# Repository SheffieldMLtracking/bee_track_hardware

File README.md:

# bee_track_hardware
The PCBs and 3d print models etc for the bee tracking system

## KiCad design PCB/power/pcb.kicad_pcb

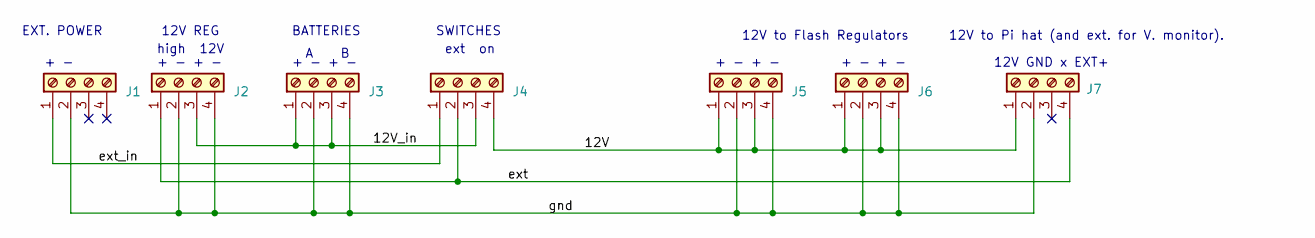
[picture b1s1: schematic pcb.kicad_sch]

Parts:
J1, J2, J3, J4, J5, J6, J7: Screw_Terminal_01x04; TerminalBlock_RND_205-00278_1x04_P5.00mm_Vertical

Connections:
/12V: J4.4, J5.1, J5.3, J6.1, J6.3, J7.1
/12V_in: J2.3, J3.1, J3.3, J4.3
/ext: J2.1, J4.2, J7.4
/ext_in: J1.1, J4.1
/gnd: J1.2, J2.2, J2.4, J3.2, J3.4, J5.2, J5.4, J6.2, J6.4, J7.2

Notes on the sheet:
high 12V
12V to Flash Regulators
12V REG
+ - + -
BATTERIES
12V to Pi hat (and ext. for V. monitor).
A B
12V GND x EXT+
EXT. POWER
ext on
+ -
SWITCHES

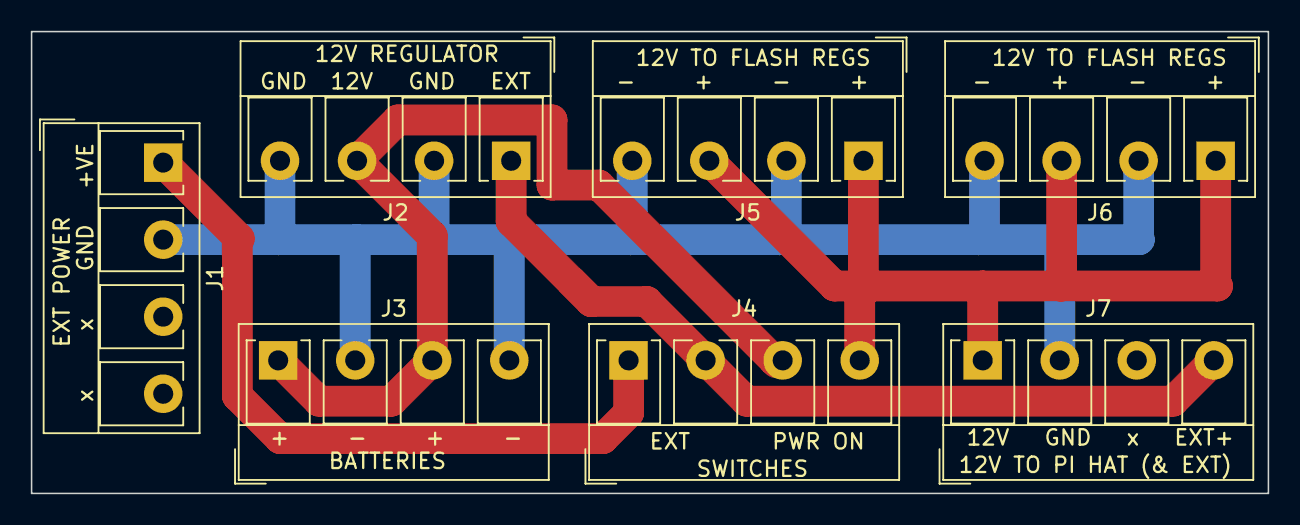
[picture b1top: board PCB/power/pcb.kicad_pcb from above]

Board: 2 copper layers, 80.3 x 30.0 mm, 7 parts (0 on the bottom side), 5 nets.

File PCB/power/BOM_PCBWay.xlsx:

|  |  | xxxx xxxx xxxxx xxPCS BOM (Sample Bill of Materials)
Item # | *Designator | *Qty | Manufacturer | *Mfg Part # | Description / Value | *Package/Footprint | Type | Your Instructions / Notes
1 | J1,J2,J3,J4,J5,J6,J7 | 7 | CAMDENBOSS | CTB5202/4 | Standard Terminal Block, Wire to Board, CTB5202, 4 Contacts, 5 mm, Terminal Blo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 | 5mm pitch, 4 pins | thru-hole | Please place with holes facing OUTWARDS. | https://uk.farnell.com/camdenboss/ctb5202-4/terminal-block-w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

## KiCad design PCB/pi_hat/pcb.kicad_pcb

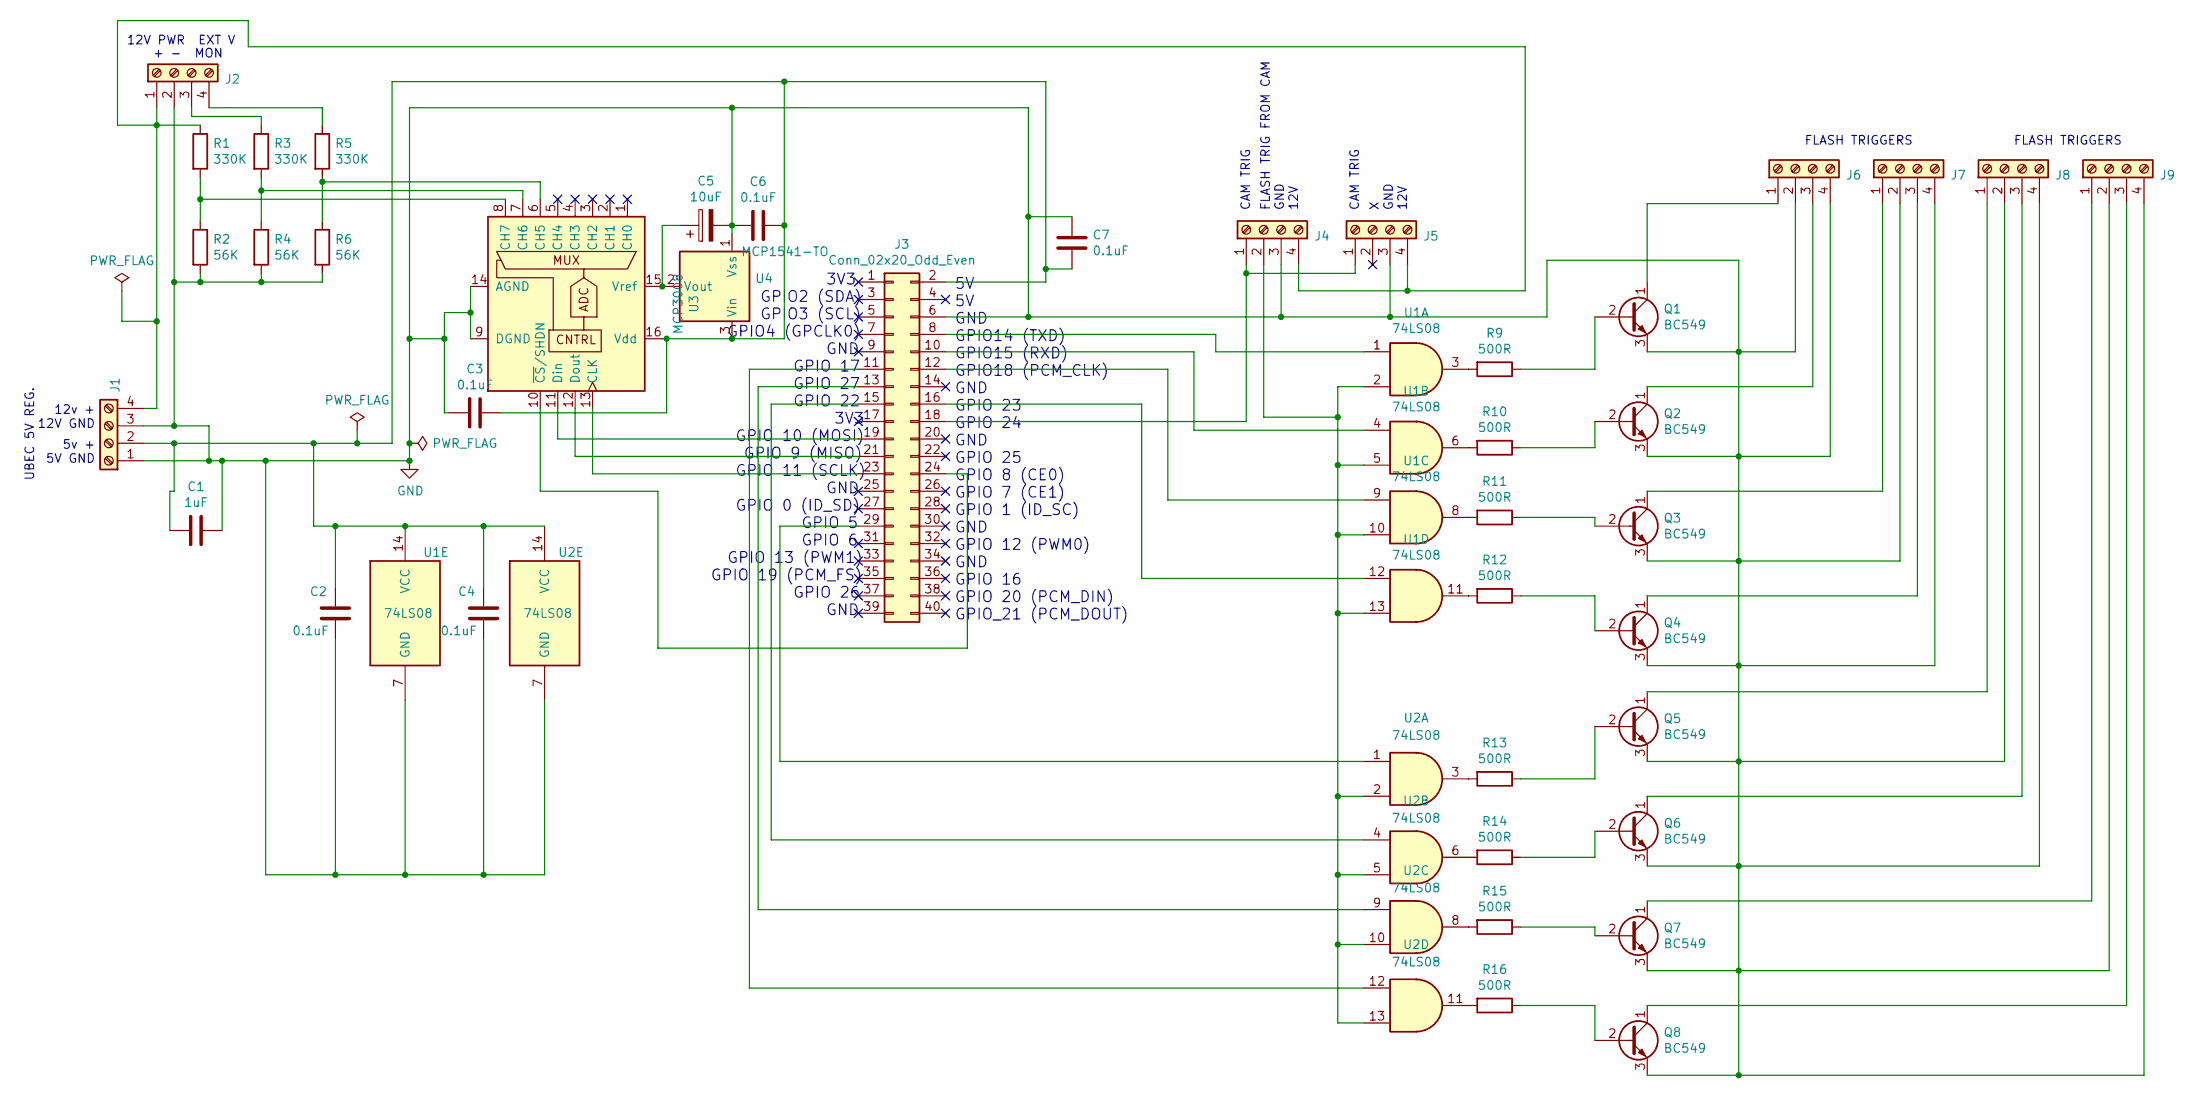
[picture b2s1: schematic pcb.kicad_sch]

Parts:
C1: 1uF; C_0402_1005Metric
C2, C3, C4, C6, C7: 0.1uF; C_0402_1005Metric
C5: 10uF; CP_Elec_4x5.4
J1, J2, J4, J5, J6, J7, J8, J9: Screw_Terminal_01x04; TerminalBlock_RND_205-00278_1x04_P5.00mm_Vertical
J3: Conn_02x20_Odd_Even; Flipped_IDC
Q1, Q2, Q3, Q4, Q5, Q6, Q7, Q8: BC549; TO-92_Inline
R1, R3, R5: 330K; R_0402_1005Metric
R2, R4, R6: 56K; R_0402_1005Metric
R9, R10, R11, R12, R13, R14, R15, R16: 500R; R_0402_1005Metric
U1, U2: 74LS08; TSSOP-14_4.4x5mm_P0.65mm
U3: MCP3008; SOIC127P600X175-16N
U4: MCP1541-TO; SOT-23-3

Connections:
GND: C1.1, C2.2, C3.2, C4.2, C5.2, C6.2, C7.1, J1.1, J1.3, J2.2, J3.6, J4.3, J5.3, J6.2, J6.4, J7.2, J7.4, J8.2, J8.4, J9.2, J9.4, Q1.3 (E), Q2.3 (E), Q3.3 (E), Q4.3 (E), Q5.3 (E), Q6.3 (E), Q7.3 (E), Q8.3 (E), R2.2, R4.2, R6.2, U1.7 (GND), U2.7 (GND), U3.9 (DGND), U3.14 (AGND), U4.1 (Vss)
unnamed: C1.2, C2.1, C3.1, C4.1, C6.1, C7.2, J1.2, J3.2, U1.14 (VCC), U2.14 (VCC), U3.16 (Vdd), U4.3 (Vin)
unnamed: J1.4, J2.1, J4.4, J5.4, R1.1
unnamed: J2.3, R3.1
unnamed: J2.4, R5.1
unnamed: J3.8, U1.1
unnamed: J3.10, U1.4
unnamed: J3.11, U2.12
unnamed: J3.12, U1.9
unnamed: J3.13, U2.9
unnamed: J3.15, U2.4
unnamed: J3.16, U1.12
unnamed: J3.18, J4.1, J5.1
unnamed: J3.19, U3.11 (Din)
unnamed: J3.21, U3.12 (Dout)
unnamed: J3.23, U3.13 (CLK)
unnamed: J3.24, U3.10 (~CS/SHDN)
unnamed: J3.29, U2.1
unnamed: J4.2, U1.2, U1.5, U1.10, U1.13, U2.2, U2.5, U2.10, U2.13
unnamed: J6.1, Q1.1 (C)
unnamed: J6.3, Q2.1 (C)
unnamed: J7.1, Q3.1 (C)
unnamed: J7.3, Q4.1 (C)
unnamed: J8.1, Q5.1 (C)
unnamed: J8.3, Q6.1 (C)
unnamed: J9.1, Q7.1 (C)
unnamed: J9.3, Q8.1 (C)
unnamed: Q1.2 (B), R9.1
unnamed: Q2.2 (B), R10.1
unnamed: Q3.2 (B), R11.1
unnamed: Q4.2 (B), R12.1
unnamed: Q5.2 (B), R13.1
unnamed: Q6.2 (B), R14.1
unnamed: Q7.2 (B), R15.1
unnamed: Q8.2 (B), R16.1
unnamed: R9.2, U1.3
unnamed: R10.2, U1.6
unnamed: R11.2, U1.8
unnamed: R12.2, U1.11
unnamed: R13.2, U2.3
unnamed: R14.2, U2.6
unnamed: R15.2, U2.8
unnamed: R16.2, U2.11
unnamed: R5.2, R6.1, U3.6 (CH5)
unnamed: R3.2, R4.1, U3.7 (CH6)
unnamed: R1.2, R2.1, U3.8 (CH7)
unnamed: C5.1, U3.15 (Vref), U4.2 (Vout)

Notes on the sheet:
FLASH TRIGGERS
+ - MON
5V 5V GND GPIO14 (TXD) GPIO15 (RXD) GPIO18 (PCM_CLK) GND GPIO 23 GPIO 24 GND GPIO 25 GPIO 8 (CE0) GPIO 7 (CE1) GPIO 1 (ID_SC) GND GPIO 12 (PWM0) GND GPIO 16 GPIO 20 (PCM_DIN) GPIO_21 (PCM_DOUT)
5v + 5V GND
X GND 12V
3V3 GPIO2 (SDA) GPIO3 (SCL) GPIO4 (GPCLK0) GND GPIO 17 GPIO 27 GPIO 22 3V3 GPIO 10 (MOSI) GPIO 9 (MISO) GPIO 11 (SCLK) GND GPIO 0 (ID_SD) GPIO 5 GPIO 6 GPIO 13 (PWM1) GPIO 19 (PCM_FS) GPIO 26 GND
FLASH TRIG FROM CAM GND 12V
UBEC 5V REG.
CAM TRIG
12V PWR EXT V
12v + 12V GND

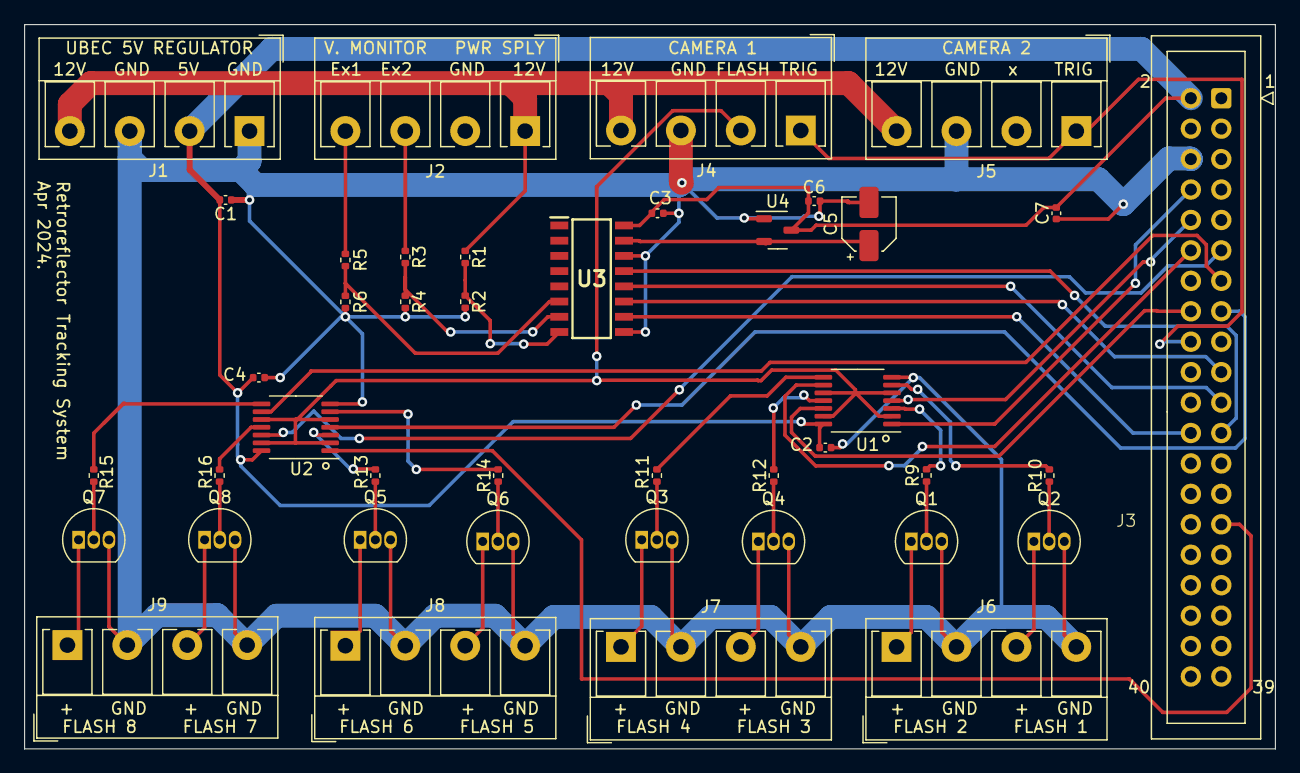
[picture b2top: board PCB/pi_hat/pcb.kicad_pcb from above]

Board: 2 copper layers, 104.4 x 60.5 mm, 42 parts (0 on the bottom side), 47 nets.

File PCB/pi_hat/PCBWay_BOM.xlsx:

|  |  | xxxx xxxx xxxxx xxPCS BOM (Sample Bill of Materials)
Item # | *Designator | *Qty | Manufacturer | *Mfg Part # | Description / Value | *Package/Footprint | Type | Your Instructions / Notes
1 | C1 | 1 | MURATA | GRM155R61E105KA12J | SMD Multilayer Ceramic Capacitor 1uF | 0402 [1005 metric] SMD | SMD |  | https://uk.farnell.com/murata/grm155r61e105ka12j/cap-1uf-25v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
2 | C2,C3,C4,C6,C7 | 5 | WALSIN | 0402X104K250CT | SMD Multilayer Ceramic Capacitor 0.1uF | 0402 [1005 metric] SMD | SMD |  | https://uk.farnell.com/walsin/0402x104k250ct/cap-0-1-f-25v-1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
3 | C5 | 1 | KEMET | EDK106M035A9BAA | SMD Aluminium Electrolytic Capacitor, Radial Can. 10 µF. | SMD | SMD | Positive indicated with + | https://uk.farnell.com/kemet/edk106m035a9baa/cap-10uf-35v-al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
4 | J1,J2,J4,J5,J6,J7,J8,J9 | 8 | CAMDENBOSS | CTB5202/4 | Standard Terminal Block, Wire to Board, CTB5202, 4 Contacts, 5 mm, Terminal Blo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 | 5mm pitch, 4 pins | thru-hole | Please place with holes facing OUTWARDS. | https://uk.farnell.com/camdenboss/ctb5202-4/terminal-block-w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
5 | J3 | 1 | WURTH ELEKTRONIK | 61304021821 | socket header; 2.54 pitch; 20 x 2 rows. | 40 contacts [20 x 2]; 2.54mm pitch | thru-hole | Symmetric (so orientation doesn’t matter) | https://uk.farnell.com/wurth-elektronik/61304021821/connecto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
6 | Q1,Q2,Q3,Q4,Q5,Q6,Q7,Q8 | 8 | Multicomp Pro | BC549C | NPN Transistors | TO-92 | thru-hole | Flat side towards edge of PCB, indicated in silk-screen (collector on left) | https://uk.farnell.com/multicomp/bc549c/transistor-npn-30v-t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
7 | R1,R3,R5 | 3 | Multicomp Pro | MCWR04X3303FTL | SMD Chip Resistor, 330K | 0402 [1005 metric] SMD | SMD |  | https://uk.farnell.com/multicomp/mcwr04x3303ftl/res-330k-1-0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
8 | R2,R4,R6 | 3 | Multicomp Pro | MCWR04X5602FTL | SMD Chip Resistor, 56K | 0402 [1005 metric] SMD | SMD |  | https://uk.farnell.com/multicomp/mcwr04x5602ftl/res-56k-1-0-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
9 | R9,R10,R11,R12,R13,R14,R15,R16 | 8 | Multicomp Pro | MCWR04X5600FTL | SMD Chip Resistor, 560R | 0402 [1005 metric] SMD | SMD |  | https://uk.farnell.com/multicomp/mcwr04x5600ftl/res-560r-1-0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
10 | U1,U2 | 2 | NEXPERIA | 74AHC08PW-Q100J | 7408 Quad 2-input AND. | 14 pin TSSOP | SMD | Pin 1 indicated by line by pad, and a circle (bottom right) | https://uk.farnell.com/nexperia/74ahc08pw-q100j/and-gate-aec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
11 | U3 | 1 | MICROCHIP | MCP3008-I/SL | Analogue to Digital Converter, Octal, 10 bit. | 16 pin SOIC | SMD | Pin 1 indicated by line next to pad (top left) | https://uk.farnell.com/microchip/mcp3008-i-sl/10bit-adc-8-ch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
12 | U4 | 1 | MICROCHIP | MCP1541T-I/TT | Voltage Reference (4.096V), MCP1541 | SOT-23-3 | SMD | Pin 1 indicated by line next to pad (top left) | https://uk.farnell.com/microchip/mcp1541t-i-tt/voltage-ref-s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
 |  |  |  |  |  |  |  | All components placed on top side

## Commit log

2024-04-17 Initial commit (send for fab. not tested)
2024-04-17 Power connections
2024-06-03 redesigned casing for retroreflector system
2024-06-18 Dimension fixes and battery holder improvements
2024-06-30 Add files via upload
    Updated 3D files with various changes made by Joe in response to previous test prints 24-30/06/24
2024-07-16 Code to run on the binary clock
2024-08-01 Rename 240712 Back cover.3mf to Orcaslicer project files/240712 Back cover.3mf
2024-08-01 Rename 240712 Side cover #001.3mf to OrcaSlicer project files/240712 Side cover #001.3mf
2024-08-01 Rename 240712 Back cover.3mf to 240712 Back cover.3mf
2024-08-01 Rename 240716 Battery stuff for half a box.3mf to OrcaSlicer project files/240716 Battery stuff for half a box.3mf
2024-08-01 Rename 240716 Circuit box.3mf to OrcaSlicer project files/240716 Circuit box.3mf
2024-08-01 Rename 240716 Main box #001.3mf to OrcaSlicer project files/240716 Main box #001.3mf
2024-08-01 Rename 240716 Main box #002.3mf to OrcaSlicer project files/240716 Main box #002.3mf
2024-08-01 Rename 240726 Camera and tripod mounts.3mf to OrcaSlicer project files/240726 Camera and tripod mounts.3mf
2024-08-01 Rename 240801 All small components for 1 box.3mf to OrcaSlicer project files/240801 All small components for 1 box.3mf
2024-08-01 Rename RetroreflectorCaseTopologyFix.FCStd to FreeCAD design files/RetroreflectorCaseTopology (Chris version).FCStd
2024-08-01 Delete RetroreflectorCaseTopologyJLW240630.FCStd
    Delete old version
2024-08-01 Rename aabattery.FCStd to FreeCAD design files/AA Battery (Mike version).FCStd
2024-08-01 Rename AA Battery (Mike version).FCStd to AABattery (Mike version).FCStd
2024-08-01 Rename AABatteryJLW2406716.FCStd to AABattery (Joe most recent version 2406716).FCStd
2024-08-01 Rename RetroreflectorCaseTopologyJLW240801.FCStd to RetroreflectorCaseTopology (Joe most recent version 240801).FCStd
2024-08-01 Rename FreeCAD design files/AA Battery.step to FreeCAD design files/Exported Step files for each component/AA Battery.step
